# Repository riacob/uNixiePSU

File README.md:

# uNixiePSU
### Description
OSHW, compact, flyback-based, nixie tube power supply\
Adjustable output from 160V to 185V, 50mA\
Size: 25x22mm 3 layer board\
Cost: standardized components, reduced cost \
Efficiency: TBD\
Noise: TBD

### Disclaimer
This project is still in development. Nothing was tested.\
This project is provided "as is" without any warranty, express or implied. By using this project, you agree that the authors and contributors are not liable for any damages, including but not limited to, hardware or software damage, personal injury, or legal liability, resulting from the use, modification, or distribution of this project. The design and implementation of high-voltage power supplies come with inherent risks. This repository is intended for educational and experimental purposes only. Users are responsible for adhering to all safety protocols, legal regulations, and guidelines when working with high-voltage electronics.

# Contributors
[Arwid Vasilev](github.com/arwidcool)
- Layout co-designer

# Gallery

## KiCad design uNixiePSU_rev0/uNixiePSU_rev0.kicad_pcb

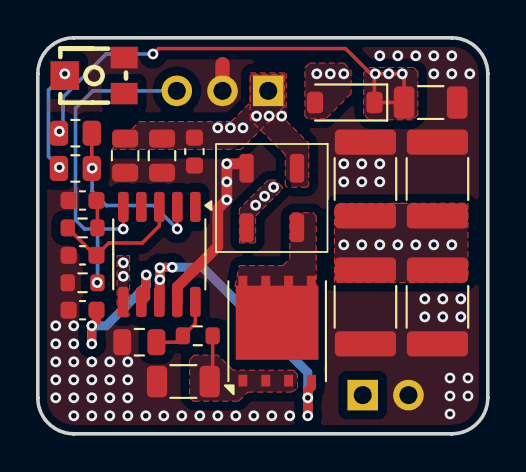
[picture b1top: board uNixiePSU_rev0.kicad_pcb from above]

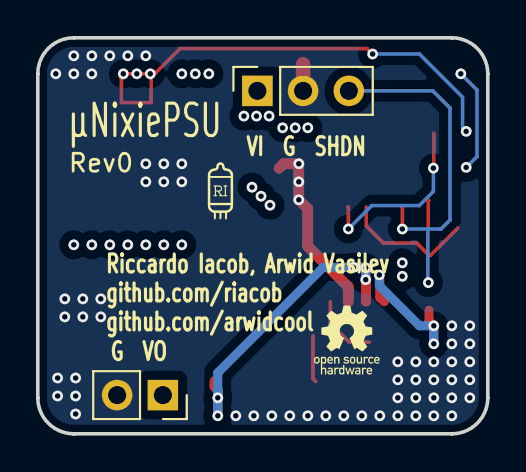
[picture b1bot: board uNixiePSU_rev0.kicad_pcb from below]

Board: 4 copper layers, 25.0 x 22.0 mm, 25 parts (2 on the bottom side), 14 nets.

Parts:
C1: 100p; C_0805_2012Metric
C2: 100n; C_1206_3216Metric
C3: 100n; C_0603_1608Metric
C4, C5: C; C_0603_1608Metric
C6: 4.7u; C_0603_1608Metric
C7, C8: 22u; C_0805_2012Metric
C9, C10, C11, C12: 1u; C_1812_4532Metric
D1: D; D_SOD-123
J1: Conn_01x03; PinSocket_1x03_P2.54mm_Vertical
J2: Conn_01x02; PinSocket_1x02_P2.54mm_Vertical
R1: 30m; R_1206_3216Metric
R2, R5: 1k; R_0603_1608Metric
R3: 100k; R_0805_2012Metric
R4: 649; R_0805_2012Metric
R6: 10k; R_0603_1608Metric
RV1: 100; RES-ADJ-SMD_VG039NCH
T1: TFM_TTRN-0630H
U1: AO_DFN-8-1EP_5.55x5.2mm_P1.27mm_EP4.12x4.6mm
U2: SSOP-10-1EP_3.9x4.9mm_P1mm_EP2.1x3.3mm

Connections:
+12V: C3.1, C7.1, C8.1, J1.1, T1.2 (AA), U2.6 (VIN)
+170V: C2.1, C9.1, C10.1, C11.1, C12.1, D1.1 (K), J2.1, R3.1
/HV_FB: R3.2, R4.1, U2.2 (FB)
/HV_SHDN: J1.3, R6.1, U2.5 (SHDN)
GND: C1.2, C2.2, C3.2, C4.2, C5.2, C6.2, C7.2, C8.2, C9.2, C10.2, C11.2, C12.2, J1.2, J2.2, R1.2, R6.2, RV1.3, T1.4 (SA), U2.9 (GND)
unnamed: C4.1, R5.2
unnamed: D1.2 (A), T1.3 (SB)
unnamed: R1.1, R2.1, U1.1 (S), U1.2 (S), U1.3 (S)
unnamed: R4.2, RV1.2
unnamed: T1.1 (AB), U1.5 (D)
unnamed: U1.4 (G), U2.8 (DRV)
unnamed: C5.1, R5.1, U2.3 (COMP)
unnamed: C1.1, R2.2, U2.10 (CS)
unnamed: C6.1, U2.7 (VCC)

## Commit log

2024-10-26 Update readme, add images
2024-10-26 Resize image
2024-10-26 Resize images
2024-10-26 Center images
2024-10-26 Add license
2024-10-26 Add disclaimer
2024-10-28 Cleanup rev0 schematic
2024-10-28 Changed license to CC BY-NC
